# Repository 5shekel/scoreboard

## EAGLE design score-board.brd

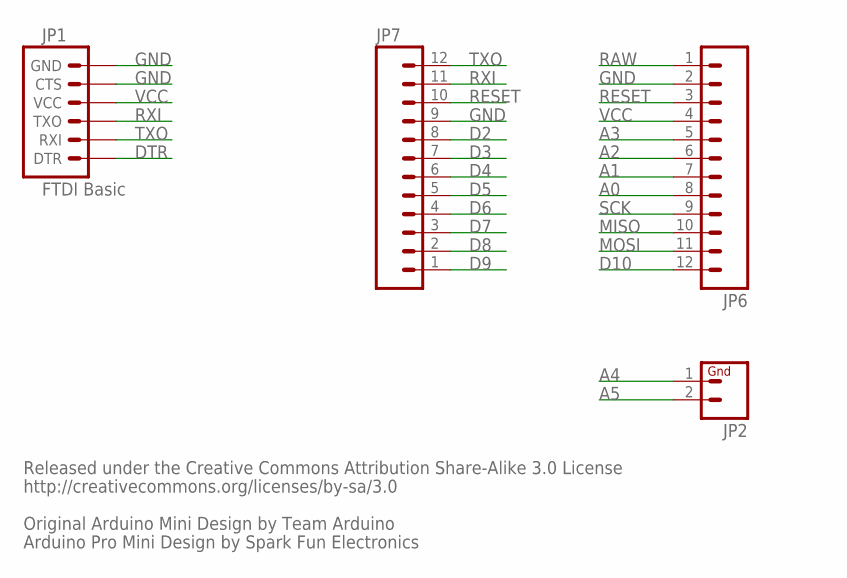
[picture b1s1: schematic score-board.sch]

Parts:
JP1: FTDI Basic; 1X06
JP2: M02PTH; 1X02
JP6, JP7: M12PTH; 1X12

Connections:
A0: JP6.8
A1: JP6.7
A2: JP6.6
A3: JP6.5
A4: JP2.1
A5: JP2.2
D2: JP7.8
D3: JP7.7
D4: JP7.6
D5: JP7.5
D6: JP7.4
D7: JP7.3
D8: JP7.2
D9: JP7.1
D10: JP6.12
DTR: JP1.1 (DTR)
GND: JP1.5 (CTS), JP1.6 (GND), JP6.2, JP7.9
MISO: JP6.10
MOSI: JP6.11
RAW: JP6.1
RESET: JP6.3, JP7.10
RXI: JP1.3 (TXO), JP7.11
SCK: JP6.9
TXO: JP1.2 (RXI), JP7.12
VCC: JP1.4 (VCC), JP6.4

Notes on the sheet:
Released under the Creative Commons Attribution Share-Alike 3.0 License
http://creativecommons.org/licenses/by-sa/3.0
Original Arduino Mini Design by Team Arduino
Arduino Pro Mini Design by Spark Fun Electronics

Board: 2 copper layers, 4 parts (4 on the bottom side), 5 nets, no tracks yet.

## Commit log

2015-04-01 fritizing
2015-04-01 looks ok, now pushing the arduino to the side for easier connection
2015-04-01 adde ard code
